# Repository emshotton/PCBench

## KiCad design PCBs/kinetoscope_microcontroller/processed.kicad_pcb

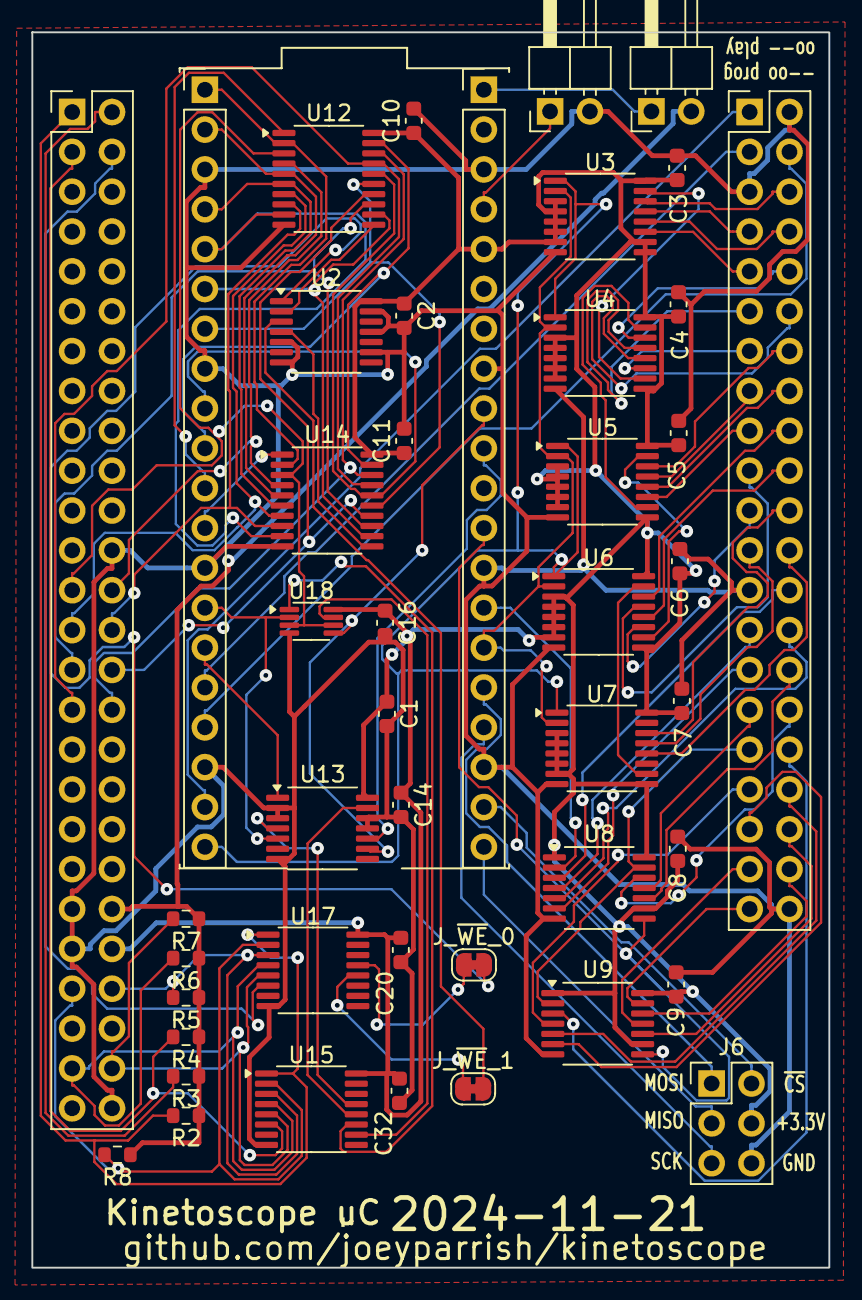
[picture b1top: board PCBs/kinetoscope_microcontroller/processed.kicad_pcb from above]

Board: 2 copper layers, 50.8 x 78.7 mm, 47 parts (0 on the bottom side), 95 nets.

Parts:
C1, C2, C3, C4, C5, C6, C7, C8, C9, C10, C11, C14, C16, C20, C32: 22nF; C_0603_1608Metric
J1: PinHeader_2x26_P2.54mm_Vertical
J2: PinHeader_2x21_P2.54mm_Vertical
J3, J4: PinHeader_1x20_P2.54mm_Vertical
J5, J7: 1x2 jumper right-angle; PinHeader_1x02_P2.54mm_Horizontal
J6: Conn_02x03_Odd_Even; PinHeader_2x03_P2.54mm_Vertical
J_~{WE}_0, J_~{WE}_1: SolderJumper-2_P1.3mm_Bridged_RoundedPad1.0x1.5mm
R2, R3, R4, R5, R6, R7, R8: 10k; R_0603_1608Metric
U2: 74AHC04; TSSOP-14_4.4x5mm_P0.65mm
U3, U4, U5, U6, U7: 74LV161A; TSSOP-16_4.4x5mm_P0.65mm
U8, U9: 74LV164A; TSSOP-14_4.4x5mm_P0.65mm
U12, U14: 74AHC373; TSSOP-20_4.4x6.5mm_P0.65mm
U13: 74AHC74; TSSOP-14_4.4x5mm_P0.65mm
U15, U17: 74LVC138A; TSSOP-16_4.4x5mm_P0.65mm
U18: 74LVC2G125; VSSOP-8_2.3x2mm_P0.5mm
X1: kinetoscope-cart-board-template
X2: Raspberry_Pi_Pico_W_template

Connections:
+3.3V: C1.1, C2.1, C3.1, C4.1, C5.1, C6.1, C7.1, C8.1, C9.1, C10.1, C11.1, C14.1, C16.1, C20.1, C32.1, J1.44 (3V), J4.5 (3V3_Out), J6.4, U2.14 (VCC), U3.3 (D0), U3.4 (D1), U3.5 (D2), U3.6 (D3), U3.7 (CEP), U3.9 (~PE), U3.10 (CET), U3.16 (VCC), U4.3 (D0), U4.4 (D1), U4.5 (D2), U4.6 (D3), U4.7 (CEP), U4.9 (~PE), U4.16 (VCC), U5.3 (D0), U5.4 (D1), U5.5 (D2), U5.6 (D3), U5.7 (CEP), U5.9 (~PE), U5.16 (VCC), U6.3 (D0), U6.4 (D1), U6.5 (D2), U6.6 (D3), U6.7 (CEP), U6.9 (~PE), U6.16 (VCC), U7.3 (D0), U7.4 (D1), U7.5 (D2), U7.6 (D3), U7.7 (CEP), U7.9 (~PE), U7.16 (VCC), U8.1 (DSA), U8.9 (~MR), U8.14 (VCC), U9.1 (DSA), U9.9 (~MR), U9.14 (VCC), U12.20 (VCC), U13.14 (VCC), U14.20 (VCC), U15.16 (VCC), U17.16 (VCC), U18.8 (VCC)
+5V: J1.42 (5V), J7.2 (B), R2.1, R3.1, R4.1, R5.1, R6.1, R7.1, R8.1
/CMD_3V: J3.14 (GP10), U13.5 (Q), U18.2
/ERR_3V: J4.9 (GP27/A1), U13.9 (Q), U18.5
/REG_EN: J4.4 (3V3_En), J5.1 (A)
/REG_R_D0: J3.1 (GP0), U12.2 (O0), U14.2 (O0)
/REG_R_D1: J3.2 (GP1), U12.5 (O1), U14.5 (O1)
/REG_R_D2: J3.4 (GP2), U12.6 (O2), U14.6 (O2)
/REG_R_D3: J3.5 (GP3), U12.9 (O3), U14.9 (O3)
/REG_R_D4: J3.6 (GP4), U12.12 (O4), U14.12 (O4)
/REG_R_D5: J3.7 (GP5), U12.15 (O5), U14.15 (O5)
/REG_R_D6: J3.9 (GP6), U12.16 (O6), U14.16 (O6)
/REG_R_D7: J3.10 (GP7), U12.19 (O7), U14.19 (O7)
/SEGA_D0: J1.25 (SEGA_D0), U12.3 (D0), U14.3 (D0), U18.3, U18.6
/SEGA_D1: J1.26 (SEGA_D1), U12.4 (D1), U14.4 (D1)
/SEGA_D2: J1.27 (SEGA_D2), U12.7 (D2), U14.7 (D2)
/SEGA_D3: J1.28 (SEGA_D3), U12.8 (D3), U14.8 (D3)
/SEGA_D4: J1.29 (SEGA_D4), U12.13 (D4), U14.13 (D4)
/SEGA_D5: J1.30 (SEGA_D5), U12.14 (D5), U14.14 (D5)
/SEGA_D6: J1.31 (SEGA_D6), U12.17 (D6), U14.17 (D6)
/SEGA_D7: J1.32 (SEGA_D7), U12.18 (D7), U14.18 (D7)
/SPI_MISO: J4.20 (GP16), J6.3
/SPI_MOSI: J4.16 (GP19), J6.1
/SPI_SCK: J4.17 (GP18), J6.5
/SRAM_DIS_0: J2.3 (SRAM_DIS_0), J3.16 (GP12)
/SRAM_DIS_1: J2.4 (SRAM_DIS_1), J3.17 (GP13)
/SRAM_D_CLK: J4.12 (GP22), U8.8 (CP), U9.8 (CP)
/SRAM_D_IN0: J2.26 (SRAM_D_IN0), U8.3 (Q0)
/SRAM_D_IN1: J2.27 (SRAM_D_IN1), U8.4 (Q1)
/SRAM_D_IN2: J2.28 (SRAM_D_IN2), U8.5 (Q2)
/SRAM_D_IN3: J2.29 (SRAM_D_IN3), U8.6 (Q3)
/SRAM_D_IN4: J2.30 (SRAM_D_IN4), U8.10 (Q4)
/SRAM_D_IN5: J2.31 (SRAM_D_IN5), U8.11 (Q5)
/SRAM_D_IN6: J2.32 (SRAM_D_IN6), U8.12 (Q6)
/SRAM_D_IN7: J2.33 (SRAM_D_IN7), U8.13 (Q7), U9.2 (DSB)
/SRAM_D_IN8: J2.34 (SRAM_D_IN8), U9.3 (Q0)
/SRAM_D_IN9: J2.35 (SRAM_D_IN9), U9.4 (Q1)
/SRAM_D_IN10: J2.36 (SRAM_D_IN10), U9.5 (Q2)
/SRAM_D_IN11: J2.37 (SRAM_D_IN11), U9.6 (Q3)
/SRAM_D_IN12: J2.38 (SRAM_D_IN12), U9.10 (Q4)
/SRAM_D_IN13: J2.39 (SRAM_D_IN13), U9.11 (Q5)
/SRAM_D_IN14: J2.40 (SRAM_D_IN14), U9.12 (Q6)
/SRAM_D_IN15: J2.41 (SRAM_D_IN15), U9.13 (Q7)
/SRAM_D_NEXT: J4.14 (GP21), U8.2 (DSB)
/SRAM_W_A0: J2.6 (SRAM_W_A0), U3.14 (Q0)
/SRAM_W_A1: J2.7 (SRAM_W_A1), U3.13 (Q1)
/SRAM_W_A2: J2.8 (SRAM_W_A2), U3.12 (Q2)
/SRAM_W_A3: J2.9 (SRAM_W_A3), U3.11 (Q3)
/SRAM_W_A4: J2.10 (SRAM_W_A4), U4.14 (Q0)
/SRAM_W_A5: J2.11 (SRAM_W_A5), U4.13 (Q1)
/SRAM_W_A6: J2.12 (SRAM_W_A6), U4.12 (Q2)
/SRAM_W_A7: J2.13 (SRAM_W_A7), U4.11 (Q3)
/SRAM_W_A8: J2.14 (SRAM_W_A8), U5.14 (Q0)
/SRAM_W_A9: J2.15 (SRAM_W_A9), U5.13 (Q1)
/SRAM_W_A10: J2.16 (SRAM_W_A10), U5.12 (Q2)
/SRAM_W_A11: J2.17 (SRAM_W_A11), U5.11 (Q3)
/SRAM_W_A12: J2.18 (SRAM_W_A12), U6.14 (Q0)
/SRAM_W_A13: J2.19 (SRAM_W_A13), U6.13 (Q1)
/SRAM_W_A14: J2.20 (SRAM_W_A14), U6.12 (Q2)
/SRAM_W_A15: J2.21 (SRAM_W_A15), U6.11 (Q3)
/SRAM_W_A16: J2.22 (SRAM_W_A16), U7.14 (Q0)
/SRAM_W_A17: J2.23 (SRAM_W_A17), U7.13 (Q1)
/SRAM_W_A18: J2.24 (SRAM_W_A18), U7.12 (Q2)
/SRAM_W_A_CLK: J4.15 (GP20), U3.2 (CP), U4.2 (CP), U5.2 (CP), U6.2 (CP), U7.2 (CP)
/VBUS: J4.1 (VBUS), J7.1 (A)
/address-counter-internal/AR0: U3.15 (TC), U4.10 (CET)
/address-counter-internal/AR1: U4.15 (TC), U5.10 (CET)
/address-counter-internal/AR2: U5.15 (TC), U6.10 (CET)
/address-counter-internal/AR3: U6.15 (TC), U7.10 (CET)
/kinetoscope-header-internal/SEGA_A1: J1.1 (SEGA_A1), R2.2, U15.1 (A0), U17.1 (A0)
/kinetoscope-header-internal/SEGA_A2: J1.2 (SEGA_A2), R3.2
/kinetoscope-header-internal/SEGA_A3: J1.3 (SEGA_A3), R4.2, U15.6 (E2)
/kinetoscope-header-internal/SEGA_A4: J1.4 (SEGA_A4), U17.6 (E2)
/register-file-internal/REG_0_WE: U2.2, U12.11 (LE)
/register-file-internal/REG_1_WE: U2.4, U14.11 (LE)
/~CMD_CLR: J3.15 (GP11), U13.1 (~R)
/~CMD_OE: U15.11 (~Y4), U18.1
/~CMD_SET: U13.4 (~S), U15.13 (~Y2)
/~ERR_CLR: U13.13 (~R), U15.12 (~Y3)
/~ERR_OE: U15.10 (~Y5), U18.7
/~ERR_SET: J4.10 (GP26/A0), U13.10 (~S)
/~REG_0_OE: J3.11 (GP8), U12.1 (OE)
/~REG_0_WE_INT: J_~{WE}_0.2 (B), U2.1
/~REG_0_WE: J_~{WE}_0.1 (A), U17.13 (~Y2)
/~REG_1_OE: J3.12 (GP9), U14.1 (OE)
/~REG_1_WE_INT: J_~{WE}_1.2 (B), U2.3
/~REG_1_WE: J_~{WE}_1.1 (A), U17.12 (~Y3)
/~SEGA_AS: J1.50 (~SEGA_AS), R7.2, U15.5 (~E1), U17.5 (~E1)
/~SEGA_OE: J1.45 (~SEGA_OE), R8.2, U15.2 (A1), U17.2 (A1)
/~SEGA_REGISTER: J1.49 (~SEGA_REGISTER), R6.2, U15.4 (~E0), U17.4 (~E0)
/~SEGA_WE_LB: J1.46 (~SEGA_WE_LB), R5.2, U15.3 (A2), U17.3 (A2)
/~SPI_CS: J4.19 (GP17), J6.2
/~SRAM_WE: J2.1 (~SRAM_WE), J3.19 (GP14)
/~SRAM_W_A_CLR: J3.20 (GP15), U3.1 (~MR), U4.1 (~MR), U5.1 (~MR), U6.1 (~MR), U7.1 (~MR)
GND: C1.2, C2.2, C3.2, C4.2, C5.2, C6.2, C7.2, C8.2, C9.2, C10.2, C11.2, C14.2, C16.2, C20.2, C32.2, J1.24 (GND), J1.41 (GND), J1.43 (GND), J1.52 (GND), J2.2 (GND), J2.5 (GND), J2.25 (GND), J2.42 (GND), J3.3 (GND), J3.8 (GND), J3.13 (GND), J3.18 (GND), J4.3 (GND), J4.8 (ADC_GND), J4.13 (GND), J4.18 (GND), J5.2 (B), J6.6, U2.5, U2.7 (GND), U2.9, U2.11, U2.13, U3.8 (GND), U4.8 (GND), U5.8 (GND), U6.8 (GND), U7.8 (GND), U8.7 (GND), U9.7 (GND), U12.10 (GND), U13.2 (D), U13.3 (C), U13.7 (GND), U13.11 (C), U13.12 (D), U14.10 (GND), U15.8 (GND), U17.8 (GND), U18.4 (GND)

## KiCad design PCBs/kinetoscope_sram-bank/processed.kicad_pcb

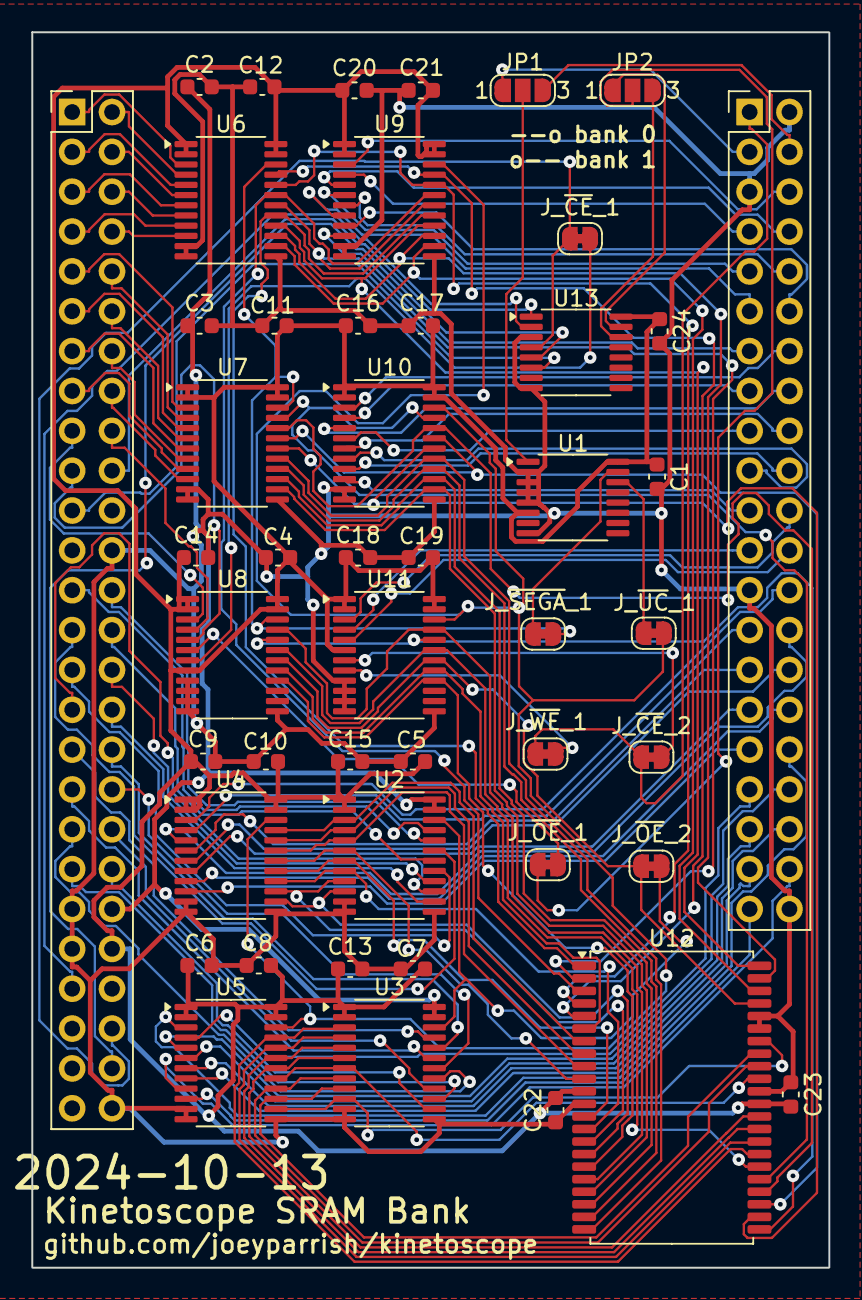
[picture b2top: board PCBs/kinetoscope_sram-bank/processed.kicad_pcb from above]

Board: 2 copper layers, 50.8 x 78.7 mm, 49 parts (0 on the bottom side), 132 nets.

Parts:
C1, C2, C3, C4, C5, C6, C7, C8, C9, C10, C11, C12, C13, C14, C15, C16, C17, C18, C19, C20, C21, C22, C23, C24: 22nF; C_0603_1608Metric
J1: PinHeader_2x26_P2.54mm_Vertical
J2: PinHeader_2x21_P2.54mm_Vertical
JP1, JP2: Jumper_3_Open; SolderJumper-3_P1.3mm_Open_RoundedPad1.0x1.5mm_NumberLabels
J_~{CE}_1, J_~{CE}_2: SolderJumper-2_P1.3mm_Bridged_RoundedPad1.0x1.5mm
J_~{OE}_1, J_~{OE}_2: SolderJumper-2_P1.3mm_Bridged_RoundedPad1.0x1.5mm
J_~{SEGA}_1: SolderJumper-2_P1.3mm_Bridged_RoundedPad1.0x1.5mm
J_~{UC}_1: SolderJumper-2_P1.3mm_Bridged_RoundedPad1.0x1.5mm
J_~{WE}_1: SolderJumper-2_P1.3mm_Bridged_RoundedPad1.0x1.5mm
U1, U13: 74LVC138A; TSSOP-16_4.4x5mm_P0.65mm
U2, U3, U4, U5, U6, U7, U8, U9, U10, U11: 74LVC8T245; TSSOP-24_4.4x7.8mm_P0.65mm
U12: IS66WV51216EBLL; TSOP-II-44_10.16x18.41mm_P0.8mm
X1: kinetoscope-cart-board-template

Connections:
+3.3V: C1.1, C4.1, C5.1, C6.1, C7.1, C8.1, C9.1, C10.1, C11.1, C12.1, C13.1, C14.1, C15.1, C16.1, C17.1, C18.1, C19.1, C20.1, C21.1, C22.2, C23.2, C24.1, J1.44 (3V), U1.6 (E2), U1.16 (VCC), U2.1 (V_{CCA}), U2.2 (DIR), U3.1 (V_{CCA}), U3.2 (DIR), U4.1 (V_{CCA}), U4.2 (DIR), U4.23 (V_{CCB}), U4.24 (V_{CCB}), U5.1 (V_{CCA}), U5.2 (DIR), U5.23 (V_{CCB}), U5.24 (V_{CCB}), U6.1 (V_{CCA}), U6.2 (DIR), U6.23 (V_{CCB}), U6.24 (V_{CCB}), U7.1 (V_{CCA}), U7.2 (DIR), U7.23 (V_{CCB}), U7.24 (V_{CCB}), U8.1 (V_{CCA}), U8.2 (DIR), U8.8 (A6), U8.23 (V_{CCB}), U8.24 (V_{CCB}), U9.1 (V_{CCA}), U9.2 (DIR), U9.23 (V_{CCB}), U9.24 (V_{CCB}), U10.1 (V_{CCA}), U10.2 (DIR), U10.23 (V_{CCB}), U10.24 (V_{CCB}), U11.1 (V_{CCA}), U11.2 (DIR), U11.6 (A4), U11.23 (V_{CCB}), U11.24 (V_{CCB}), U12.11 (VDD_1), U12.33 (VDD_2), U13.16 (VCC)
+5V: C2.1, C3.1, J1.42 (5V), U2.23 (V_{CCB}), U2.24 (V_{CCB}), U3.23 (V_{CCB}), U3.24 (V_{CCB})
/SEGA_A1: J1.1 (SEGA_A1), U6.3 (A1)
/SEGA_A2: J1.2 (SEGA_A2), U6.4 (A2)
/SEGA_A3: J1.3 (SEGA_A3), U6.5 (A3)
/SEGA_A4: J1.4 (SEGA_A4), U6.6 (A4)
/SEGA_A5: J1.5 (SEGA_A5), U6.7 (A5)
/SEGA_A6: J1.6 (SEGA_A6), U6.8 (A6)
/SEGA_A7: J1.7 (SEGA_A7), U6.9 (A7)
/SEGA_A8: J1.8 (SEGA_A8), U6.10 (A8)
/SEGA_A9: J1.9 (SEGA_A9), U7.3 (A1)
/SEGA_A10: J1.10 (SEGA_A10), U7.4 (A2)
/SEGA_A11: J1.11 (SEGA_A11), U7.5 (A3)
/SEGA_A12: J1.12 (SEGA_A12), U7.6 (A4)
/SEGA_A13: J1.13 (SEGA_A13), U7.7 (A5)
/SEGA_A14: J1.14 (SEGA_A14), U7.8 (A6)
/SEGA_A15: J1.15 (SEGA_A15), U7.9 (A7)
/SEGA_A16: J1.16 (SEGA_A16), U7.10 (A8)
/SEGA_A17: J1.17 (SEGA_A17), U8.3 (A1)
/SEGA_A18: J1.18 (SEGA_A18), U8.4 (A2)
/SEGA_A19: J1.19 (SEGA_A19), U8.5 (A3)
/SEGA_A20: J1.20 (SEGA_A20), U13.1 (A0)
/SEGA_A21: J1.21 (SEGA_A21), U13.6 (E2)
/SEGA_D0: J1.25 (SEGA_D0), U2.21 (B1)
/SEGA_D1: J1.26 (SEGA_D1), U2.20 (B2)
/SEGA_D2: J1.27 (SEGA_D2), U2.19 (B3)
/SEGA_D3: J1.28 (SEGA_D3), U2.18 (B4)
/SEGA_D4: J1.29 (SEGA_D4), U2.17 (B5)
/SEGA_D5: J1.30 (SEGA_D5), U2.16 (B6)
/SEGA_D6: J1.31 (SEGA_D6), U2.15 (B7)
/SEGA_D7: J1.32 (SEGA_D7), U2.14 (B8)
/SEGA_D8: J1.33 (SEGA_D8), U3.21 (B1)
/SEGA_D9: J1.34 (SEGA_D9), U3.20 (B2)
/SEGA_D10: J1.35 (SEGA_D10), U3.19 (B3)
/SEGA_D11: J1.36 (SEGA_D11), U3.18 (B4)
/SEGA_D12: J1.37 (SEGA_D12), U3.17 (B5)
/SEGA_D13: J1.38 (SEGA_D13), U3.16 (B6)
/SEGA_D14: J1.39 (SEGA_D14), U3.15 (B7)
/SEGA_D15: J1.40 (SEGA_D15), U3.14 (B8)
/SRAM_A0: U6.21 (B1), U9.21 (B1), U12.5 (A0)
/SRAM_A1: U6.20 (B2), U9.20 (B2), U12.4 (A1)
/SRAM_A2: U6.19 (B3), U9.19 (B3), U12.3 (A2)
/SRAM_A3: U6.18 (B4), U9.18 (B4), U12.2 (A3)
/SRAM_A4: U6.17 (B5), U9.17 (B5), U12.1 (A4)
/SRAM_A5: U6.16 (B6), U9.16 (B6), U12.44 (A5)
/SRAM_A6: U6.15 (B7), U9.15 (B7), U12.43 (A6)
/SRAM_A7: U6.14 (B8), U9.14 (B8), U12.42 (A7)
/SRAM_A8: U7.21 (B1), U10.21 (B1), U12.27 (A8)
/SRAM_A9: U7.20 (B2), U10.20 (B2), U12.26 (A9)
/SRAM_A10: U7.19 (B3), U10.19 (B3), U12.25 (A10)
/SRAM_A11: U7.18 (B4), U10.18 (B4), U12.24 (A11)
/SRAM_A12: U7.17 (B5), U10.17 (B5), U12.22 (A12)
/SRAM_A13: U7.16 (B6), U10.16 (B6), U12.21 (A13)
/SRAM_A14: U7.15 (B7), U10.15 (B7), U12.20 (A14)
/SRAM_A15: U7.14 (B8), U10.14 (B8), U12.19 (A15)
/SRAM_A16: U8.21 (B1), U11.21 (B1), U12.18 (A16)
/SRAM_A17: U8.20 (B2), U11.20 (B2), U12.23 (A17)
/SRAM_A18: U8.19 (B3), U11.19 (B3), U12.28 (A18)
/SRAM_DATA0: U2.3 (A1), U4.21 (B1), U12.7 (I/O0)
/SRAM_DATA1: U2.4 (A2), U4.20 (B2), U12.8 (I/O1)
/SRAM_DATA2: U2.5 (A3), U4.19 (B3), U12.9 (I/O2)
/SRAM_DATA3: U2.6 (A4), U4.18 (B4), U12.10 (I/O3)
/SRAM_DATA4: U2.7 (A5), U4.17 (B5), U12.13 (I/O4)
/SRAM_DATA5: U2.8 (A6), U4.16 (B6), U12.14 (I/O5)
/SRAM_DATA6: U2.9 (A7), U4.15 (B7), U12.15 (I/O6)
/SRAM_DATA7: U2.10 (A8), U4.14 (B8), U12.16 (I/O7)
/SRAM_DATA8: U3.3 (A1), U5.21 (B1), U12.29 (I/O8)
/SRAM_DATA9: U3.4 (A2), U5.20 (B2), U12.30 (I/O9)
/SRAM_DATA10: U3.5 (A3), U5.19 (B3), U12.31 (I/O10)
/SRAM_DATA11: U3.6 (A4), U5.18 (B4), U12.32 (I/O11)
/SRAM_DATA12: U3.7 (A5), U5.17 (B5), U12.35 (I/O12)
/SRAM_DATA13: U3.8 (A6), U5.16 (B6), U12.36 (I/O13)
/SRAM_DATA14: U3.9 (A7), U5.15 (B7), U12.37 (I/O14)
/SRAM_DATA15: U3.10 (A8), U5.14 (B8), U12.38 (I/O15)
/SRAM_DIS: JP1.2 (C), U1.1 (A0)
/SRAM_DIS_0: J2.3 (SRAM_DIS_0), JP1.1 (A)
/SRAM_DIS_1: J2.4 (SRAM_DIS_1), JP1.3 (B)
/SRAM_D_IN0: J2.26 (SRAM_D_IN0), U4.3 (A1)
/SRAM_D_IN1: J2.27 (SRAM_D_IN1), U4.4 (A2)
/SRAM_D_IN2: J2.28 (SRAM_D_IN2), U4.5 (A3)
/SRAM_D_IN3: J2.29 (SRAM_D_IN3), U4.6 (A4)
/SRAM_D_IN4: J2.30 (SRAM_D_IN4), U4.7 (A5)
/SRAM_D_IN5: J2.31 (SRAM_D_IN5), U4.8 (A6)
/SRAM_D_IN6: J2.32 (SRAM_D_IN6), U4.9 (A7)
/SRAM_D_IN7: J2.33 (SRAM_D_IN7), U4.10 (A8)
/SRAM_D_IN8: J2.34 (SRAM_D_IN8), U5.3 (A1)
/SRAM_D_IN9: J2.35 (SRAM_D_IN9), U5.4 (A2)
/SRAM_D_IN10: J2.36 (SRAM_D_IN10), U5.5 (A3)
/SRAM_D_IN11: J2.37 (SRAM_D_IN11), U5.6 (A4)
/SRAM_D_IN12: J2.38 (SRAM_D_IN12), U5.7 (A5)
/SRAM_D_IN13: J2.39 (SRAM_D_IN13), U5.8 (A6)
/SRAM_D_IN14: J2.40 (SRAM_D_IN14), U5.9 (A7)
/SRAM_D_IN15: J2.41 (SRAM_D_IN15), U5.10 (A8)
/SRAM_W_A0: J2.6 (SRAM_W_A0), U9.3 (A1)
/SRAM_W_A1: J2.7 (SRAM_W_A1), U9.4 (A2)
/SRAM_W_A2: J2.8 (SRAM_W_A2), U9.5 (A3)
/SRAM_W_A3: J2.9 (SRAM_W_A3), U9.6 (A4)
/SRAM_W_A4: J2.10 (SRAM_W_A4), U9.7 (A5)
/SRAM_W_A5: J2.11 (SRAM_W_A5), U9.8 (A6)
/SRAM_W_A6: J2.12 (SRAM_W_A6), U9.9 (A7)
/SRAM_W_A7: J2.13 (SRAM_W_A7), U9.10 (A8)
/SRAM_W_A8: J2.14 (SRAM_W_A8), U10.3 (A1)
/SRAM_W_A9: J2.15 (SRAM_W_A9), U10.4 (A2)
/SRAM_W_A10: J2.16 (SRAM_W_A10), U10.5 (A3)
/SRAM_W_A11: J2.17 (SRAM_W_A11), U10.6 (A4)
/SRAM_W_A12: J2.18 (SRAM_W_A12), U10.7 (A5)
/SRAM_W_A13: J2.19 (SRAM_W_A13), U10.8 (A6)
/SRAM_W_A14: J2.20 (SRAM_W_A14), U10.9 (A7)
/SRAM_W_A15: J2.21 (SRAM_W_A15), U10.10 (A8)
/SRAM_W_A16: J2.22 (SRAM_W_A16), U11.3 (A1)
/SRAM_W_A17: J2.23 (SRAM_W_A17), U11.4 (A2)
/SRAM_W_A18: J2.24 (SRAM_W_A18), U11.5 (A3)
/~SEGA_AS: J1.50 (~SEGA_AS), U13.5 (~E1)
/~SEGA_CE: J1.48 (~SEGA_CE), J_~{CE}_1.1 (A), U13.4 (~E0)
/~SEGA_CONTROL_INT: J_~{SEGA}_1.2 (B), U6.22 (~OE), U7.22 (~OE), U8.22 (~OE)
/~SEGA_CONTROL: J_~{SEGA}_1.1 (A), U1.15 (~Y0)
/~SEGA_OE: J1.45 (~SEGA_OE), U13.2 (A1)
/~SRAM_BUFFER_OE_INT: J_~{OE}_2.2 (B), U2.22 (~OE), U3.22 (~OE)
/~SRAM_CE_READ_INT: J_~{CE}_1.2 (B), U8.7 (A5)
/~SRAM_CE_WRITE_INT: J_~{CE}_2.2 (B), U11.7 (A5)
/~SRAM_FINAL_CE: U8.17 (B5), U11.17 (B5), U12.6 (~CS1)
/~SRAM_FINAL_OE: J_~{OE}_2.1 (A), U8.18 (B4), U11.18 (B4), U12.41 (~OE)
/~SRAM_FINAL_WE: U8.16 (B6), U11.16 (B6), U12.17 (~WE)
/~SRAM_OE0: JP2.1 (A), U13.15 (~Y0)
/~SRAM_OE1: JP2.3 (B), U13.14 (~Y1)
/~SRAM_OE_INT: J_~{OE}_1.2 (B), U8.6 (A4)
/~SRAM_OE: JP2.2 (C), J_~{OE}_1.1 (A)
/~SRAM_WE_INT: J_~{WE}_1.2 (B), U11.8 (A6)
/~SRAM_WE: J2.1 (~SRAM_WE), J_~{CE}_2.1 (A), J_~{WE}_1.1 (A)
/~UC_CONTROL_INT: J_~{UC}_1.2 (B), U4.22 (~OE), U5.22 (~OE), U9.22 (~OE), U10.22 (~OE), U11.22 (~OE)
/~UC_CONTROL: J_~{UC}_1.1 (A), U1.14 (~Y1)
GND: C1.2, C2.2, C3.2, C4.2, C5.2, C6.2, C7.2, C8.2, C9.2, C10.2, C11.2, C12.2, C13.2, C14.2, C15.2, C16.2, C17.2, C18.2, C19.2, C20.2, C21.2, C22.1, C23.1, C24.2, J1.24 (GND), J1.41 (GND), J1.43 (GND), J1.52 (GND), J2.2 (GND), J2.5 (GND), J2.25 (GND), J2.42 (GND), U1.2 (A1), U1.3 (A2), U1.4 (~E0), U1.5 (~E1), U1.8 (GND), U2.11 (GND), U2.12 (GND), U2.13 (GND), U3.11 (GND), U3.12 (GND), U3.13 (GND), U4.11 (GND), U4.12 (GND), U4.13 (GND), U5.11 (GND), U5.12 (GND), U5.13 (GND), U6.11 (GND), U6.12 (GND), U6.13 (GND), U7.11 (GND), U7.12 (GND), U7.13 (GND), U8.9 (A7), U8.10 (A8), U8.11 (GND), U8.12 (GND), U8.13 (GND), U9.11 (GND), U9.12 (GND), U9.13 (GND), U10.11 (GND), U10.12 (GND), U10.13 (GND), U11.9 (A7), U11.10 (A8), U11.11 (GND), U11.12 (GND), U11.13 (GND), U12.12 (GND_1), U12.34 (GND_2), U12.39 (~LB), U12.40 (~UB), U13.3 (A2), U13.8 (GND)

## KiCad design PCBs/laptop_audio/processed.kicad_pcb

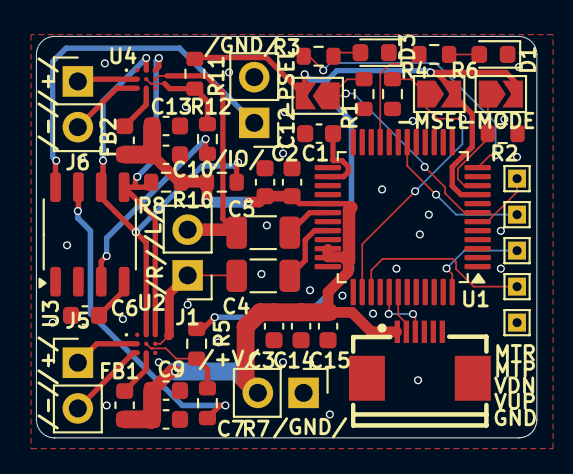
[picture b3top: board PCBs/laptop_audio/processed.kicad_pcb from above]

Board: 2 copper layers, 27.8 x 22.3 mm, 46 parts (0 on the bottom side), 35 nets.

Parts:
C1, C3, C6, C7, C10, C15: 100nF; C_0603_1608Metric
C2, C12, C14: 4.7uF; C_0603_1608Metric
C4, C5: 100uF (C1954161); C_1206_3216Metric
C9, C13: 10uF; C_0603_1608Metric
D1: REC_MUTE; LED_0603_1608Metric
D3: OPER; LED_0603_1608Metric
FB1, FB2: GZ1608D601TF; L_0603_1608Metric
J1, J7: SPK; PinHeader_1x02_P2.54mm_Vertical
J3: USB; FPC-SMD_6P-P0.50_XUNPU_FPC-05F-6PH20
J4: PWR; PinHeader_1x02_P2.54mm_Vertical
J5: SPKR; PinHeader_1x02_P2.54mm_Vertical
J6: SPKL; PinHeader_1x02_P2.54mm_Vertical
JP1: PSEL; SolderJumper-2_P1.3mm_Open_TrianglePad1.0x1.5mm
JP2: MODE; SolderJumper-2_P1.3mm_Open_TrianglePad1.0x1.5mm
JP3: MSEL; SolderJumper-2_P1.3mm_Open_TrianglePad1.0x1.5mm
R1, R2, R3, R4, R5, R6, R8, R10, R11: 10k; R_0603_1608Metric
R7, R12: 0R; R_0603_1608Metric
TP1, TP2, TP3, TP4, TP5: TestPoint; TestPoint_THTPad_1.0x1.0mm_Drill0.5mm
U1: CM108; LQFP-48_7x7mm_P0.5mm
U2, U4: TPA2028
U3: CH32V003JxMx; SOP-8_3.9x4.9mm_P1.27mm

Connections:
+3.3V: JP1.2 (B), JP2.2 (B), JP3.2 (B), R5.2, R11.2, U1.9 (DREG33)
/AMP_L: R12.2, U3.3 (PA2)
/AMP_R: R7.2, U3.7 (PC4)
/AUDIO_L: C5.2, J1.2, U4.B3 (IN+)
/AUDIO_R: C4.2, J1.1, U2.B3 (IN+)
/D+: J3.3, U1.41 (USBDP)
/D-: J3.2, U1.42 (USBDM)
/LEDO: R3.1, U1.12 (LEDO)
/LEDR: R6.1, U1.21 (LEDR)
/MODE: JP2.1 (A), R2.2, U1.10 (MODE)
/MSEL: JP3.1 (A), R4.2, U1.38 (MSEL)
/MUTEP: TP2.1, U1.18 (MUTEP)
/MUTER: TP1.1, U1.6 (MUTER)
/PWRSEL: JP1.1 (A), R1.2, U1.7 (PWRSEL)
/SCL: R10.1, U2.A2 (SCL), U3.6 (PC2), U4.A2 (SCL)
/SDA: R8.1, U2.A3 (SDA), U3.5 (PC1), U4.A3 (SDA)
/SWIO: J7.1, U3.8 (PD1/PD4/PD5)
/VOLDN: TP3.1, U1.48 (VOLDN)
/VOLUP: TP4.1, U1.39 (VOLUP)
GND: C1.2, C2.2, C3.2, C6.2, C7.2, C9.2, C10.2, C12.1, C13.2, C14.2, C15.2, D1.1 (K), D3.1 (K), J3.6, J3.MP (MountPin), J4.1, J7.2, R1.1, R2.1, R4.1, TP5.1, U1.14 (DVSS1), U1.16 (SDIN), U1.22 (ADSEL), U1.23 (TEST), U1.24 (AVSS1), U1.33 (AVSS2), U1.36 (DVSS2), U2.A1 (PGND), U2.C3 (IN-), U3.2 (VSS), U4.A1 (PGND), U4.C3 (IN-)
unnamed: D1.2 (A), R6.2
unnamed: D3.2 (A), R3.2
unnamed: J5.1, U2.B1 (OUT+)
unnamed: J5.2, U2.C1 (OUT-)
unnamed: J6.1, U4.B1 (OUT+)
unnamed: J6.2, U4.C1 (OUT-)
unnamed: C5.1, U1.30 (LOL)
unnamed: C4.1, U1.32 (LOR)
unnamed: C12.2, U1.26 (VREF)
unnamed: R5.1, R7.1, U2.B2 (EN)
unnamed: FB1.1, U2.C2 (PVDD)
unnamed: C6.1, U3.4 (VDD)
unnamed: R11.1, R12.1, U4.B2 (EN)
unnamed: FB2.1, U4.C2 (PVDD)
VBUS: C1.1, C2.1, C3.1, C7.1, C9.1, C10.1, C13.1, C14.1, C15.1, FB1.2, FB2.2, J3.1, J4.2, R8.2, R10.2, U1.29 (AVDD1), U1.34 (AVDD2), U1.35 (DVDD)

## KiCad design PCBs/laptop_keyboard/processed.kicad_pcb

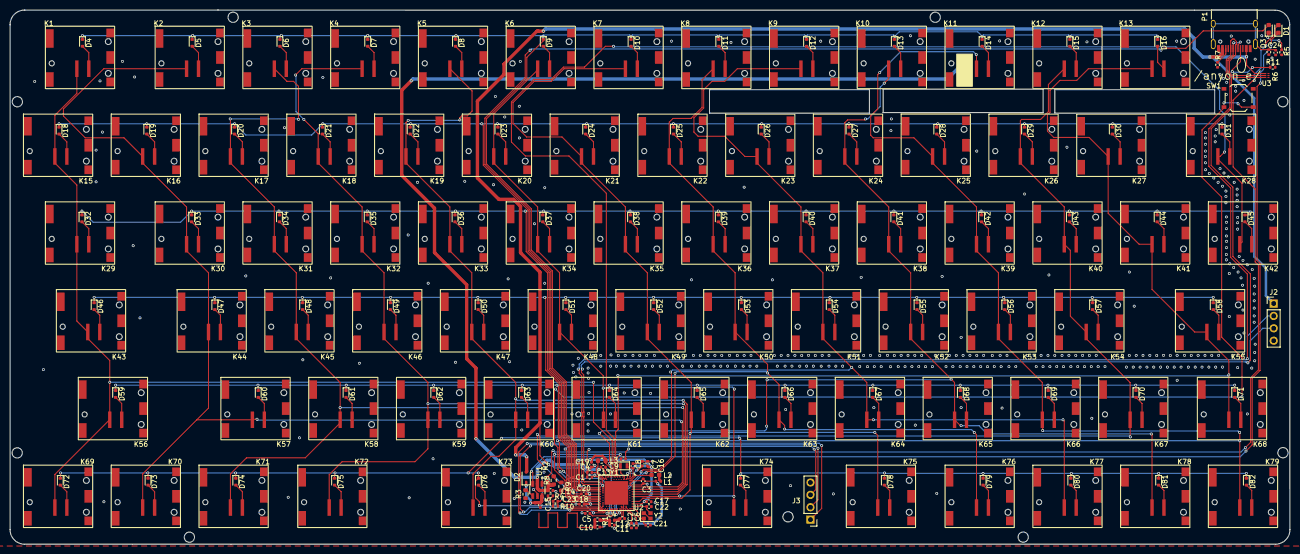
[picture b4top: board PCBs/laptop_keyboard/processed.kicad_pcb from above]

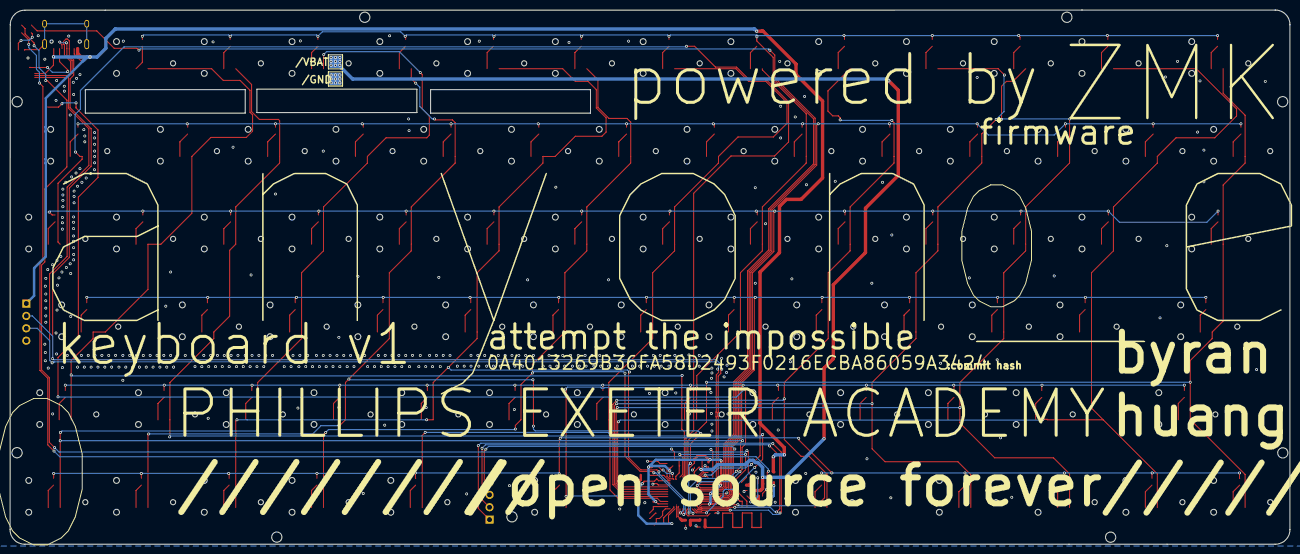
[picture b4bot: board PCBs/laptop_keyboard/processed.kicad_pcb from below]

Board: 2 copper layers, 262.5 x 109.5 mm, 220 parts (2 on the bottom side), 136 nets.

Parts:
AE1: Antenna; 2.4GHz-meander-antenna-v2
C1, C4, C13, C19: 4.7uF; C_0402_1005Metric
C2, C14, C15, C20: 1uF; C_0402_1005Metric
C3: 47nF; C_0402_1005Metric
C5: 1nF; C_0402_1005Metric
C6: 100pF; C_0402_1005Metric
C7, C16, C17, C18: 100nF; C_0402_1005Metric
C8, C9, C21, C22: 15pF; C_0402_1005Metric
C10: 1.5pF; C_0402_1005Metric
C11, C12: 1pF; C_0402_1005Metric
C23: 10nF; C_0402_1005Metric
C24: 1000pF/NC; C_0402_1005Metric
D1: CHG; LED_0603_1608Metric
D2: B5819W SL; D_SOD-323
D3: BLUE; LED_0603_1608Metric
D4, D5, D6, D7, D8, D9, D10, D11, D12, D13, D14, D15, D16, D18, D19, D20, D21, D22, D23, D24, D25, D26, D27, D28, D29, D30, D31, D32, D33, D34, D35, D36, D37, D38, D39, D40, D41, D42, D43, D44, D45, D46, D47, D48, D49, D50, D51, D52, D53, D54, D55, D56, D57, D58, D59, D60, D61, D62, D63, D64, D65, D66, D67, D68, D69, D70, D71, D72, D73, D74, D75, D76, D77, D78, D79, D80, D81, D82: D; D_SOD-523
H9, H10, H11, H13, H14, H16, H18, H20, H21: M2; M2_No_Padding
J2: USB POGO; PinHeader_1x04_P2.54mm_Vertical
J3: Debug; PinHeader_1x04_P2.54mm_Vertical
K1: Esc; Cherry_ULP_SMD
K2: F1; Cherry_ULP_SMD
K3: F2; Cherry_ULP_SMD
K4: F3; Cherry_ULP_SMD
K5: F4; Cherry_ULP_SMD
K6: F5; Cherry_ULP_SMD
K7: F6; Cherry_ULP_SMD
K8: F7; Cherry_ULP_SMD
K9: F8; Cherry_ULP_SMD
K10: F9; Cherry_ULP_SMD
K11: F10; Cherry_ULP_SMD
K12: F11; Cherry_ULP_SMD
K13: F12; Cherry_ULP_SMD
K15: ~~,`; Cherry_ULP_SMD
K16: !,1; Cherry_ULP_SMD
K17: @,2; Cherry_ULP_SMD
K18: #,3; Cherry_ULP_SMD
K19: $,4; Cherry_ULP_SMD
K20: %,5; Cherry_ULP_SMD
K21: ^,6; Cherry_ULP_SMD
K22: &,7; Cherry_ULP_SMD
K23: *,8; Cherry_ULP_SMD
K24: (,9; Cherry_ULP_SMD
K25: ),0; Cherry_ULP_SMD
K26: _,-; Cherry_ULP_SMD
K27: +,=; Cherry_ULP_SMD
K28: Backspace; Cherry_ULP_SMD
K29: Tab; Cherry_ULP_SMD
K30: Q; Cherry_ULP_SMD
K31: W; Cherry_ULP_SMD
K32: E; Cherry_ULP_SMD
K33: R; Cherry_ULP_SMD
K34: T; Cherry_ULP_SMD
K35: Y; Cherry_ULP_SMD
K36: U; Cherry_ULP_SMD
K37: I; Cherry_ULP_SMD
K38: O; Cherry_ULP_SMD
K39: P; Cherry_ULP_SMD
K40: {,[; Cherry_ULP_SMD
K41: },]; Cherry_ULP_SMD
K42: |,\; Cherry_ULP_SMD
K43: Caps Lock; Cherry_ULP_SMD
K44: A; Cherry_ULP_SMD
K45: S; Cherry_ULP_SMD
K46: D; Cherry_ULP_SMD
K47: F; Cherry_ULP_SMD
K48: G; Cherry_ULP_SMD
K49: H; Cherry_ULP_SMD
K50: J; Cherry_ULP_SMD
K51: K; Cherry_ULP_SMD
K52: L; Cherry_ULP_SMD
K53: :,;; Cherry_ULP_SMD
K54: ",'; Cherry_ULP_SMD
K55: Enter; Cherry_ULP_SMD
K56, K68: Shift; Cherry_ULP_SMD
K57: Z; Cherry_ULP_SMD
K58: X; Cherry_ULP_SMD
K59: C; Cherry_ULP_SMD
K60: V; Cherry_ULP_SMD
K61: B; Cherry_ULP_SMD
K62: N; Cherry_ULP_SMD
K63: M; Cherry_ULP_SMD
K64: <,,; Cherry_ULP_SMD
K65: >,.; Cherry_ULP_SMD
K66: ?,/; Cherry_ULP_SMD
K67: ↑; Cherry_ULP_SMD
K69: Fn; Cherry_ULP_SMD
K70: Ctrl; Cherry_ULP_SMD
K71, K76: Alt; Cherry_ULP_SMD
K72, K75: Meta; Cherry_ULP_SMD
K73, K74: Space; Cherry_ULP_SMD
K77: ←; Cherry_ULP_SMD
K78: ↓; Cherry_ULP_SMD
K79: →; Cherry_ULP_SMD
L1: 15nH; L_0402_1005Metric
L2, L3: 10uH; L_0603_1608Metric
L4: 3.9nH; L_0402_1005Metric
NT1: NetTie_2; net-tie-2-tiny
P1: USB-C; USB_C_Receptacle_HRO_TYPE-C-31-M-12
R1: 0R; R_0402_1005Metric
R2, R4: 10k; R_0402_1005Metric
R3: 2.7k; R_0603_1608Metric
R5: 1.5k; R_0402_1005Metric
R6, R7: 5.1k; R_0402_1005Metric
R8, R9: 2M; R_0603_1608Metric
R10: 10M; R_0402_1005Metric
R11: 1M; R_0402_1005Metric
SW1: Reset; SW_Push_1P1T_XKB_TS-1187A
TP5: VBAT; TestPoint_Pad_2.5x2.5mm
TP6: BAT GND; TestPoint_Pad_2.5x2.5mm
U1: BQ21040DBVR; SOT95P280X145-6N
U2: nRF52840; Nordic_AQFN-73-1EP_7x7mm_P0.5mm
U3: ESDR0502NMUTAG; UDFN-6_1.2x1.0mm_P0.4mm
Y1: 32.768 kHz; Crystal_SMD_2012-2Pin_2.0x1.2mm
Y2: 32MHz; Crystal_SMD_2016-4Pin_2.0x1.6mm

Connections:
/Key Matrix/Col_0: K1.1, K15.1, K29.1, K43.1, K56.1, K69.1, U2.U1 (TRACEDATA1/P0.12)
/Key Matrix/Col_1: K2.1, K16.1, K30.1, K44.1, K57.1, K70.1, U2.A8 (AIN7/P0.31)
/Key Matrix/Col_2: K3.1, K17.1, K31.1, K45.1, K58.1, K71.1, U2.A10 (AIN5/P0.29)
/Key Matrix/Col_3: K4.1, K18.1, K32.1, K46.1, K59.1, K72.1, U2.A12 (AIN0/P0.02)
/Key Matrix/Col_4: K5.1, K19.1, K33.1, K47.1, K60.1, K73.1, U2.A14 (P1.15)
/Key Matrix/Col_5: K6.1, K20.1, K34.1, K48.1, K61.1, K74.1, U2.A16 (P1.13)
/Key Matrix/Col_6: K7.1, K21.1, K35.1, K49.1, K62.1, K75.1, U2.A20 (P1.10)
/Key Matrix/Col_7: K8.1, K22.1, K36.1, K50.1, K63.1, K76.1, U2.J24 (NFC2/P0.10)
/Key Matrix/Col_8: K9.1, K23.1, K37.1, K51.1, K64.1, K77.1, U2.L24 (NFC1/P0.09)
/Key Matrix/Col_9: K10.1, K24.1, K38.1, K52.1, K65.1, K78.1, U2.R24 (P1.06)
/Key Matrix/Col_10: K11.1, K25.1, K39.1, K53.1, K66.1, K79.1, U2.U24 (P1.04)
/Key Matrix/Col_11: K12.1, K26.1, K40.1, K54.1, K67.1, U2.W24 (P1.02)
/Key Matrix/Col_12: K13.1, K27.1, K41.1, K55.1, K68.1, U2.L1 (P0.06)
/Key Matrix/Col_13: K28.1, K42.1, U2.N1 (P0.08)
/Key Matrix/Row_0: D4.1 (K), D5.1 (K), D6.1 (K), D7.1 (K), D8.1 (K), D9.1 (K), D10.1 (K), D11.1 (K), D12.1 (K), D13.1 (K), D14.1 (K), D15.1 (K), D16.1 (K), U2.AD8 (P0.13)
/Key Matrix/Row_1: D18.1 (K), D19.1 (K), D20.1 (K), D21.1 (K), D22.1 (K), D23.1 (K), D24.1 (K), D25.1 (K), D26.1 (K), D27.1 (K), D28.1 (K), D29.1 (K), D30.1 (K), D31.1 (K), U2.AD12 (P0.17)
/Key Matrix/Row_2: D32.1 (K), D33.1 (K), D34.1 (K), D35.1 (K), D36.1 (K), D37.1 (K), D38.1 (K), D39.1 (K), D40.1 (K), D41.1 (K), D42.1 (K), D43.1 (K), D44.1 (K), D45.1 (K), U2.AD16 (P0.20)
/Key Matrix/Row_3: D46.1 (K), D47.1 (K), D48.1 (K), D49.1 (K), D50.1 (K), D51.1 (K), D52.1 (K), D53.1 (K), D54.1 (K), D55.1 (K), D56.1 (K), D57.1 (K), D58.1 (K), U2.AD18 (P0.22)
/Key Matrix/Row_4: D59.1 (K), D60.1 (K), D61.1 (K), D62.1 (K), D63.1 (K), D64.1 (K), D65.1 (K), D66.1 (K), D67.1 (K), D68.1 (K), D69.1 (K), D70.1 (K), D71.1 (K), U2.AD20 (P0.24)
/Key Matrix/Row_5: D72.1 (K), D73.1 (K), D74.1 (K), D75.1 (K), D76.1 (K), D77.1 (K), D78.1 (K), D79.1 (K), D80.1 (K), D81.1 (K), D82.1 (K), U2.AC21 (P0.25)
/nRF52840/ANT: AE1.1 (A), C10.2, R1.2
/nRF52840/CC1: P1.A5 (CC), R6.1
/nRF52840/CC2: P1.B5 (VCONN), R7.1
BAT_VOLT: C23.2, R9.2, R10.1, U2.J1 (AIN2/P0.04)
BLUE_LED: D3.2 (A), U2.AD10 (P0.15)
GND: C1.1, C2.1, C3.1, C4.2, C5.2, C6.2, C7.2, C8.1, C9.1, C10.1, C11.1, C13.1, C14.2, C15.2, C16.1, C17.1, C18.1, C19.1, C20.1, C21.2, C22.2, C23.1, C24.2, J2.4, J3.4, NT1.2, P1.A1 (GND), P1.A12 (GND), P1.B1 (GND), P1.B12 (GND), R3.1, R4.1, R5.1, R6.2, R7.2, R10.2, R11.1, SW1.2, TP6.1, U1.5 (GND), U2.B7 (VSS), U2.EP (VSS), U3.1 (GND), Y2.2, Y2.4
unnamed: C11.2, L4.1, R1.1
unnamed: D1.2 (A), R2.2
unnamed: D1.1 (K), U1.3 (~CHG)
unnamed: C15.1, D2.1 (K), U1.6 (VIN)
unnamed: D3.1 (K), R5.2
unnamed: D4.2 (A), K1.2
unnamed: D5.2 (A), K2.2
unnamed: D6.2 (A), K3.2
unnamed: D7.2 (A), K4.2
unnamed: D8.2 (A), K5.2
unnamed: D9.2 (A), K6.2
unnamed: D10.2 (A), K7.2
unnamed: D11.2 (A), K8.2
unnamed: D12.2 (A), K9.2
unnamed: D13.2 (A), K10.2
unnamed: D14.2 (A), K11.2
unnamed: D15.2 (A), K12.2
unnamed: D16.2 (A), K13.2
unnamed: D18.2 (A), K15.2
unnamed: D19.2 (A), K16.2
unnamed: D20.2 (A), K17.2
unnamed: D21.2 (A), K18.2
unnamed: D22.2 (A), K19.2
unnamed: D23.2 (A), K20.2
unnamed: D24.2 (A), K21.2
unnamed: D25.2 (A), K22.2
unnamed: D26.2 (A), K23.2
unnamed: D27.2 (A), K24.2
unnamed: D28.2 (A), K25.2
unnamed: D29.2 (A), K26.2
unnamed: D30.2 (A), K27.2
unnamed: D31.2 (A), K28.2
unnamed: D32.2 (A), K29.2
unnamed: D33.2 (A), K30.2
unnamed: D34.2 (A), K31.2
unnamed: D35.2 (A), K32.2
unnamed: D36.2 (A), K33.2
unnamed: D37.2 (A), K34.2
unnamed: D38.2 (A), K35.2
unnamed: D39.2 (A), K36.2
unnamed: D40.2 (A), K37.2
unnamed: D41.2 (A), K38.2
unnamed: D42.2 (A), K39.2
unnamed: D43.2 (A), K40.2
unnamed: D44.2 (A), K41.2
unnamed: D45.2 (A), K42.2
unnamed: D46.2 (A), K43.2
unnamed: D47.2 (A), K44.2
unnamed: D48.2 (A), K45.2
unnamed: D49.2 (A), K46.2
unnamed: D50.2 (A), K47.2
unnamed: D51.2 (A), K48.2
unnamed: D52.2 (A), K49.2
unnamed: D53.2 (A), K50.2
unnamed: D54.2 (A), K51.2
unnamed: D55.2 (A), K52.2
unnamed: D56.2 (A), K53.2
unnamed: D57.2 (A), K54.2
unnamed: D58.2 (A), K55.2
unnamed: D59.2 (A), K56.2
unnamed: D60.2 (A), K57.2
unnamed: D61.2 (A), K58.2
unnamed: D62.2 (A), K59.2
unnamed: D63.2 (A), K60.2
unnamed: D64.2 (A), K61.2
unnamed: D65.2 (A), K62.2
unnamed: D66.2 (A), K63.2
unnamed: D67.2 (A), K64.2
unnamed: D68.2 (A), K65.2
unnamed: D69.2 (A), K66.2
unnamed: D70.2 (A), K67.2
unnamed: D71.2 (A), K68.2
unnamed: D72.2 (A), K69.2
unnamed: D73.2 (A), K70.2
unnamed: D74.2 (A), K71.2
unnamed: D75.2 (A), K72.2
unnamed: D76.2 (A), K73.2
unnamed: D77.2 (A), K74.2
unnamed: D78.2 (A), K75.2
unnamed: D79.2 (A), K76.2
unnamed: D80.2 (A), K77.2
unnamed: D81.2 (A), K78.2
unnamed: D82.2 (A), K79.2
unnamed: L1.2, L2.1
unnamed: C24.1, P1.S1 (SHIELD), R11.2
unnamed: R8.2, R9.1
unnamed: R3.2, U1.4 (ISET)
unnamed: R4.2, U1.1 (TS)
unnamed: C12.2, L4.2, U2.H23 (ANT)
unnamed: L2.2, U2.B3 (DCC)
unnamed: L3.2, U2.AB2 (DCCH)
unnamed: C7.1, U2.C1 (DEC1)
unnamed: C6.1, U2.D23 (DEC3)
unnamed: C2.2, C3.2, L1.1, U2.B5 (DEC4), U2.E24 (DEC6)
unnamed: C5.1, U2.N24 (DEC5)
unnamed: C4.1, U2.AC5 (DECUSB)
unnamed: C21.1, U2.B24 (XC1), Y2.1
unnamed: C22.1, U2.A23 (XC2), Y2.3
unnamed: C8.2, U2.D2 (XL1/P0.00), Y1.1
unnamed: C9.2, U2.F2 (XL2/P0.01), Y1.2
RESET: SW1.1, U2.AC9 (P0.14), U2.AC11 (P0.16), U2.AC13 (P0.18/~RESET)
SWC: J3.1, U2.AA24 (SWDCLK)
SWD: J3.2, U2.AC24 (SWDIO)
SWO: J3.3, U2.AD22 (TRACEDATA0/P1.00)
USB_D+: J2.2, P1.A6 (D+), P1.B6 (D+), U2.AD6 (D+), U3.5 (D+)
USB_D-: J2.3, P1.A7 (D-), P1.B7 (D-), U2.AD4 (D-), U3.6 (VBUS)
VBAT: C13.2, C14.1, R2.1, R8.1, TP5.1, U1.2 (OUT), U2.Y2 (VDDH)
VBUS: C1.2, D2.2 (A), J2.1, P1.A4 (VBUS), P1.A9 (VBUS), P1.B4 (VBUS), P1.B9 (VBUS), U2.AD2 (VBUS), U3.4 (D-)
VDD_NRF: C16.2, C17.2, C18.2, C19.2, C20.2, L3.1, U2.A22 (VDD), U2.AD14 (VDD), U2.AD23 (VDD), U2.B1 (VDD), U2.W1 (VDD)
VSS_PA: C12.1, NT1.1, U2.F23 (VSS_PA)
